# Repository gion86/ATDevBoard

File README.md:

# ATDevBoard
Atmel developement board for ATMega and ATTiny X4/X5

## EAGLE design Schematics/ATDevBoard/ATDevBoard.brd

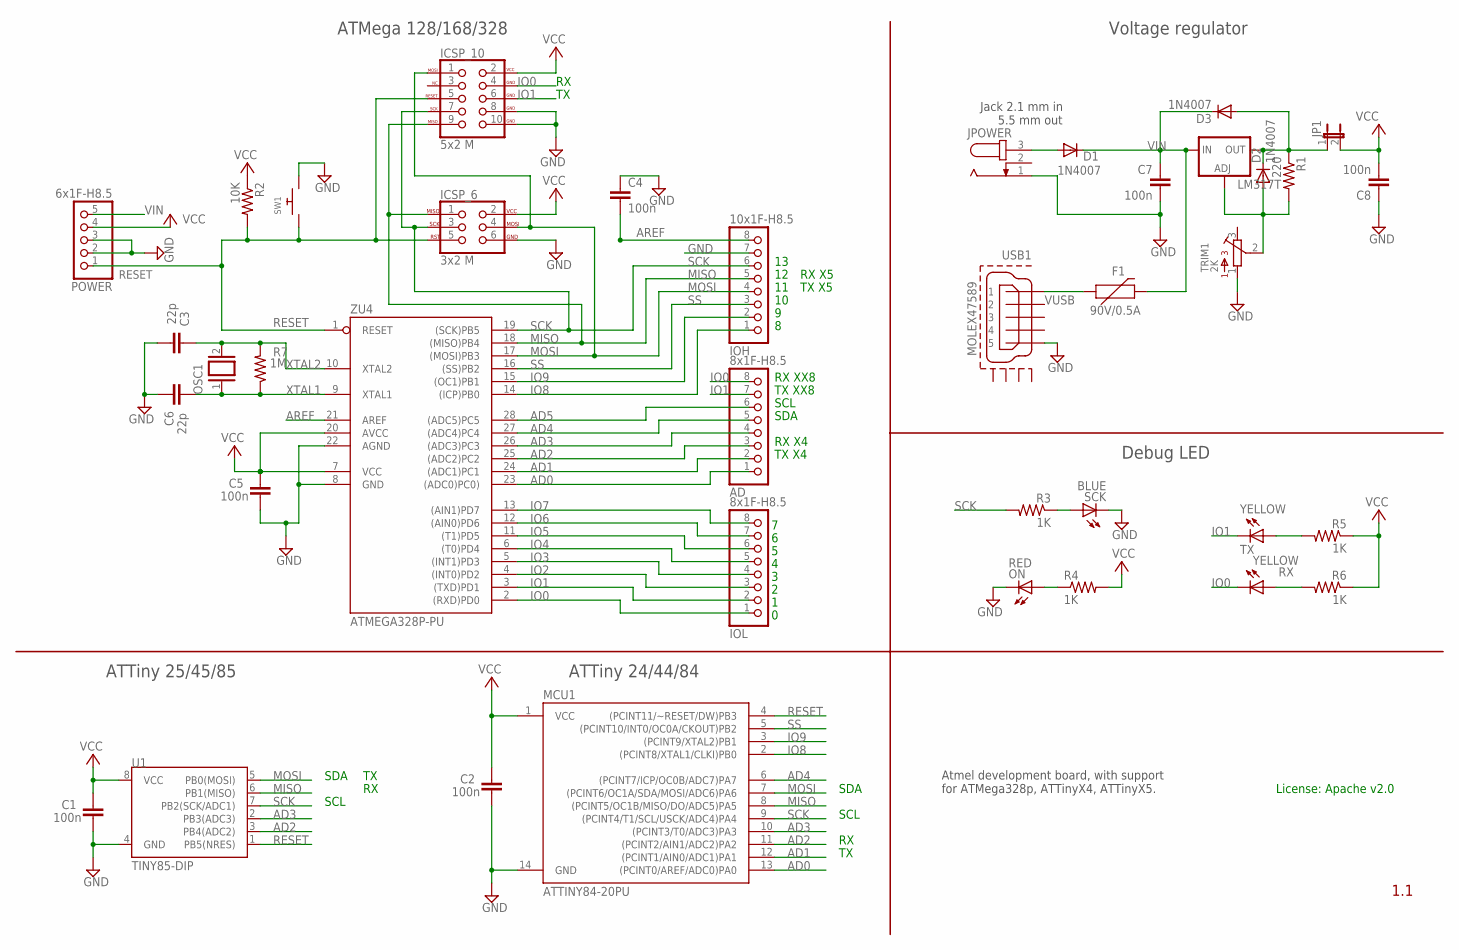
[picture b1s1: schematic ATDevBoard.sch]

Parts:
AD: 8x1F-H8.5; 1X08
C1, C2, C4, C5, C7, C8: 100n; C050-024X044
C3, C6: 22p; C050-024X044
D1, D2, D3: 1N4007; DO41-10
F1: 90V/0.5A; PTH
ICSP_6: 3x2 M; 2X3
ICSP_10: 5x2 M; 2X5-SHROUDED
IOH: 10x1F-H8.5; 1X08
IOL: 8x1F-H8.5; 1X08
JP1: JP1E; JP1
JPOWER: JACK-PLUG0; SPC4077
LM317T: LM317TS; 317TS
MCU1: ATTINY84-20PU; DIL14
ON: RED; CHIPLED_1206
OSC1: XTAL/S; QS
POWER: 6x1F-H8.5; 1X05
R1: 220; 0204/7
R2: 10K; 0309/12
R3, R4, R5, R6: 1K; 0207/10
R7: 1M; 0309/12
RX: YELLOW; CHIPLED_1206
SCK: BLUE; CHIPLED_1206
SW1: SWITCH_PUSHBUTTONEVQ-PE; TACT_PANA-EVQ
TRIM1: 2K; 3362R
TX: YELLOW; CHIPLED_1206
U1: TINY85-DIP; DIP08
USB1: MOLEX47589; 47589-0001
ZU4: ATMEGA328P-PU; DIL28-3

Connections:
AD0: AD.1, MCU1.13 ((PCINT0/AREF/ADC0)PA0), ZU4.23 ((ADC0)PC0))
AD1: AD.2, MCU1.12 ((PCINT1/AIN0/ADC1)PA1), ZU4.24 ((ADC1)PC1)
AD2: AD.3, MCU1.11 ((PCINT2/AIN1/ADC2)PA2), U1.3 (PB4(ADC2)), ZU4.25 ((ADC2)PC2)
AD3: AD.4, MCU1.10 ((PCINT3/T0/ADC3)PA3), U1.2 (PB3(ADC3)), ZU4.26 ((ADC3)PC3)
AD4: AD.5, MCU1.6 ((PCINT7/ICP/OC0B/ADC7)PA7), ZU4.27 ((ADC4)PC4)
AD5: AD.6, ZU4.28 ((ADC5)PC5)
AREF: C4.2, IOH.8, ZU4.21 (AREF)
GND: C1.1, C2.1, C3.1, C4.1, C5.1, C6.2, C7.1, C8.1, ICSP_6.6, ICSP_10.8 (GND), ICSP_10.10 (GND), IOH.7, JPOWER.1, MCU1.14 (GND), ON.C, POWER.2, POWER.3, SCK.C, SW1.P$2, TRIM1.1, U1.4 (GND), USB1.5, ZU4.8 (GND), ZU4.22 (AGND)
IO0: AD.8, ICSP_10.4 (GND), IOL.1, RX.C, ZU4.2 ((RXD)PD0)
IO1: AD.7, ICSP_10.6 (GND), IOL.2, TX.C, ZU4.3 ((TXD)PD1)
IO2: IOL.3, ZU4.4 ((INT0)PD2)
IO3: IOL.4, ZU4.5 ((INT1)PD3)
IO4: IOL.5, ZU4.6 ((T0)PD4)
IO5: IOL.6, ZU4.11 ((T1)PD5)
IO6: IOL.7, ZU4.12 ((AIN0)PD6)
IO7: IOL.8, ZU4.13 ((AIN1)PD7)
IO8: IOH.1, MCU1.2 ((PCINT8/XTAL1/CLKI)PB0), ZU4.14 ((ICP)PB0)
IO9: IOH.2, MCU1.3 ((PCINT9/XTAL2)PB1), ZU4.15 ((OC1)PB1)
MISO: ICSP_6.1, ICSP_10.9 (MISO), IOH.5, MCU1.8 ((PCINT5/OC1B/MISO/DO/ADC5)PA5), U1.6 (PB1(MISO)), ZU4.18 ((MISO)PB4)
MOSI: ICSP_6.4, ICSP_10.1 (MOSI), IOH.4, MCU1.7 ((PCINT6/OC1A/SDA/MOSI/ADC6)PA6), U1.5 (PB0(MOSI)), ZU4.17 ((MOSI)PB3)
unnamed: D2.A, LM317T.1 (ADJ), R1.2, TRIM1.2
unnamed: D1.A, JPOWER.3
unnamed: ON.A, R4.1
unnamed: R3.1, SCK.A
unnamed: D2.C, D3.A, JP1.1, LM317T.2 (OUT), R1.1
unnamed: R6.2, RX.A
unnamed: R5.2, TX.A
RESET: ICSP_6.5, ICSP_10.5 (RESET), MCU1.4 ((PCINT11/~RESET/DW)PB3), POWER.1, R2.2, SW1.P$1, U1.1 (PB5(NRES)), ZU4.1 (RESET)
SCK: ICSP_6.3, ICSP_10.7 (SCK), IOH.6, MCU1.9 ((PCINT4/T1/SCL/USCK/ADC4)PA4), R3.2, U1.7 (PB2(SCK/ADC1)), ZU4.19 ((SCK)PB5)
SS: IOH.3, MCU1.5 ((PCINT10/INT0/OC0A/CKOUT)PB2), ZU4.16 ((SS)PB2)
VCC: C1.2, C2.2, C5.2, C8.2, ICSP_6.2, ICSP_10.2 (VCC), JP1.2, MCU1.1 (VCC), POWER.4, R2.1, R4.2, R5.1, R6.1, U1.8 (VCC), ZU4.7 (VCC), ZU4.20 (AVCC)
VIN: C7.2, D1.C, D3.C, F1.P$2 (2), LM317T.3 (IN), POWER.5
VUSB: F1.P$1 (1), USB1.1
XTAL1: C6.1, OSC1.1, R7.1, ZU4.9 (XTAL1)
XTAL2: C3.2, OSC1.2, R7.2, ZU4.10 (XTAL2)

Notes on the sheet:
Voltage regulator
TX XX8
RX XX8
SDA
SCL
Jack 2.1 mm in 5.5 mm out
Debug LED
ATTiny 24/44/84
ATTiny 25/45/85
ATMega 128/168/328
TX X5
RX X5
RX X4
TX X4
Atmel development board, with support for ATMega328p, ATTinyX4, ATTinyX5.
License: Apache v2.0

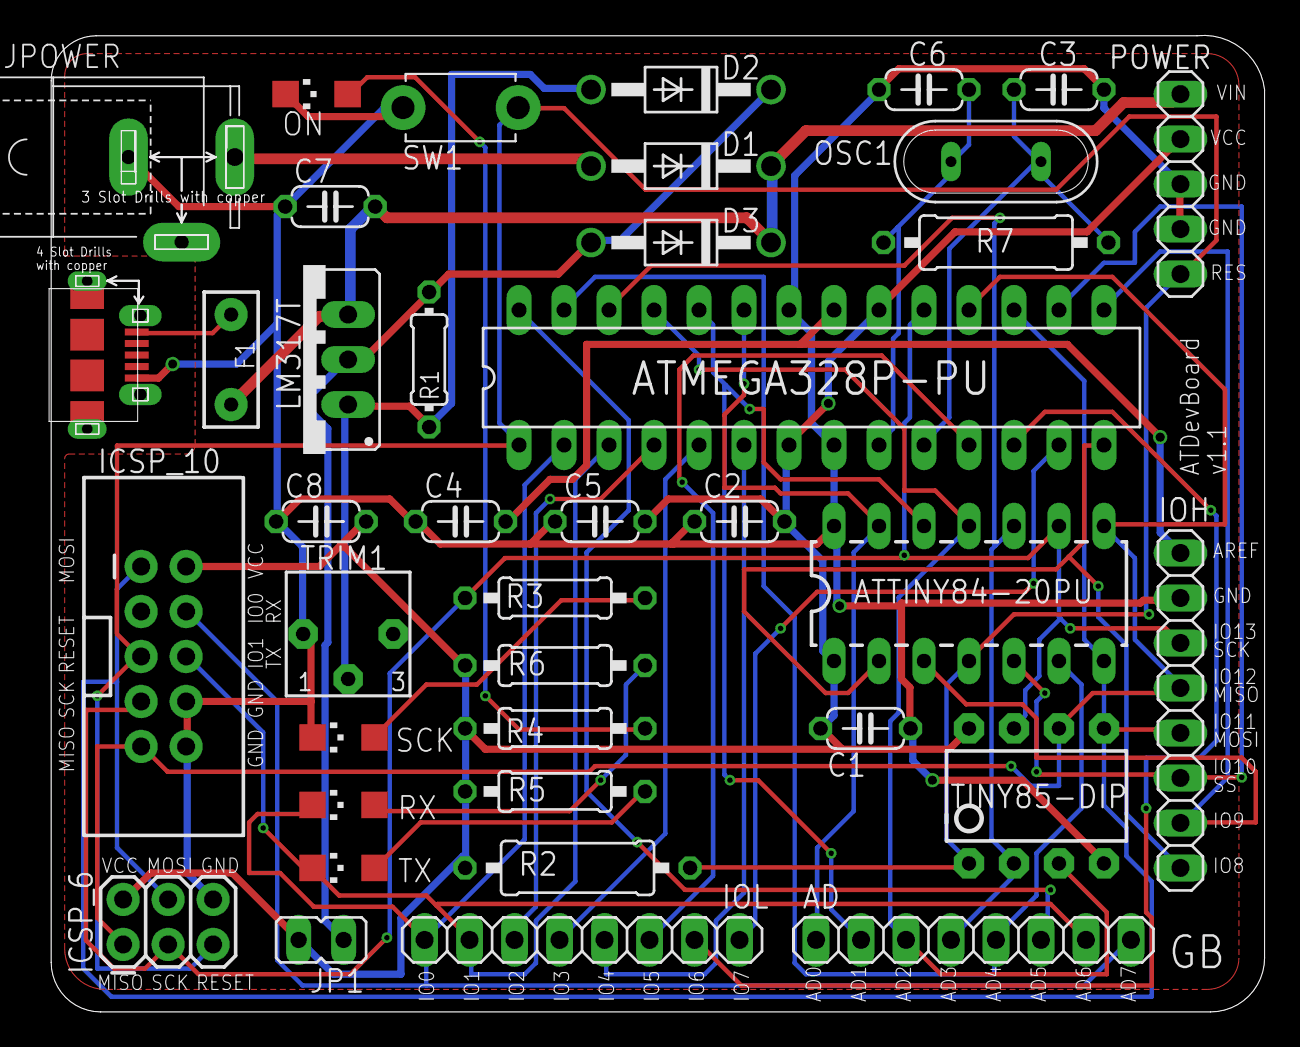
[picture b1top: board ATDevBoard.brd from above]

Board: 2 copper layers, 69.3 x 55.0 mm, 39 parts (0 on the bottom side), 35 nets.

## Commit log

2018-03-31 Added initial version of schematic and board, with partlist
2018-04-22 Added vaule for regulator resistors, first routed version of brd. Added pdfs for brd and schematic.
2018-04-22 Added gerber files for SeeedStudio
2018-04-25 Fixed packages for some resistors, replaced 1N4004 with 1N4007 diodes
2018-04-28 Fixed some components package with buy info, revisited board layout.
2018-04-29 Added micro USB, trimmer and PTC fuse
2018-04-29 Added plated slot for DC plug, new device for micro USB connector, updated partlist
2018-04-29 Fixed package for trimmer
2018-04-30 Replaced Dc plug with component in CuSTOM_GB library
2018-05-01 Changed size of power header to 5, added label for all signals in/out
2018-05-01 Removed diode for reset line, revisted layout for oscillator
2018-05-02 Replaced USB micro connector with Molex one
2018-05-05 Updated partlist
2018-05-13 Fidex schematic for trimmer, added jumper for VCC, schematic tested on breadboard
2018-05-17 Added fist version of gerber file for SeeedStudio
2018-06-05 Modified cutout slots for DC connector and micro USB, reviewed name texts in tNames level. Made gerber file for board v1.0, ready for SeeedStudio
2018-06-08 Added text message for slot drills on board file
2018-06-12 Rerun cam on brd file to upload to SeeedStudio, deleted PNG folder
2018-09-11 Fixed 1M resistor package, and header distance in PCB
2018-09-11 Rerun CAM processor on PCB v1.1

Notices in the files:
parts and their libraries:
SparkFun-Connectors: Licensing: Creative Commons ShareAlike 4.0 International - https://creativecommons.org/licenses/by-sa/4.0
CuSTOM_GB: (C) 2014 Tomasz Boleslaw CEDRO, cederom@tlen.pl, http://www.tomek.cedro.info.
